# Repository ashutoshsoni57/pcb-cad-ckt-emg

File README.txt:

Autodesk EAGLE based EMG filtering circuit with
dual layer PCB Design.

Size:- 6x6 cm (length x breadth)
Reference 3D CAD images attached (Prepared from Fusion 360 pushed from EAGLE)

For printing check Toner Transfer Images.
Ground Polygon
Export BoM as required

Project under MIT LICENSE

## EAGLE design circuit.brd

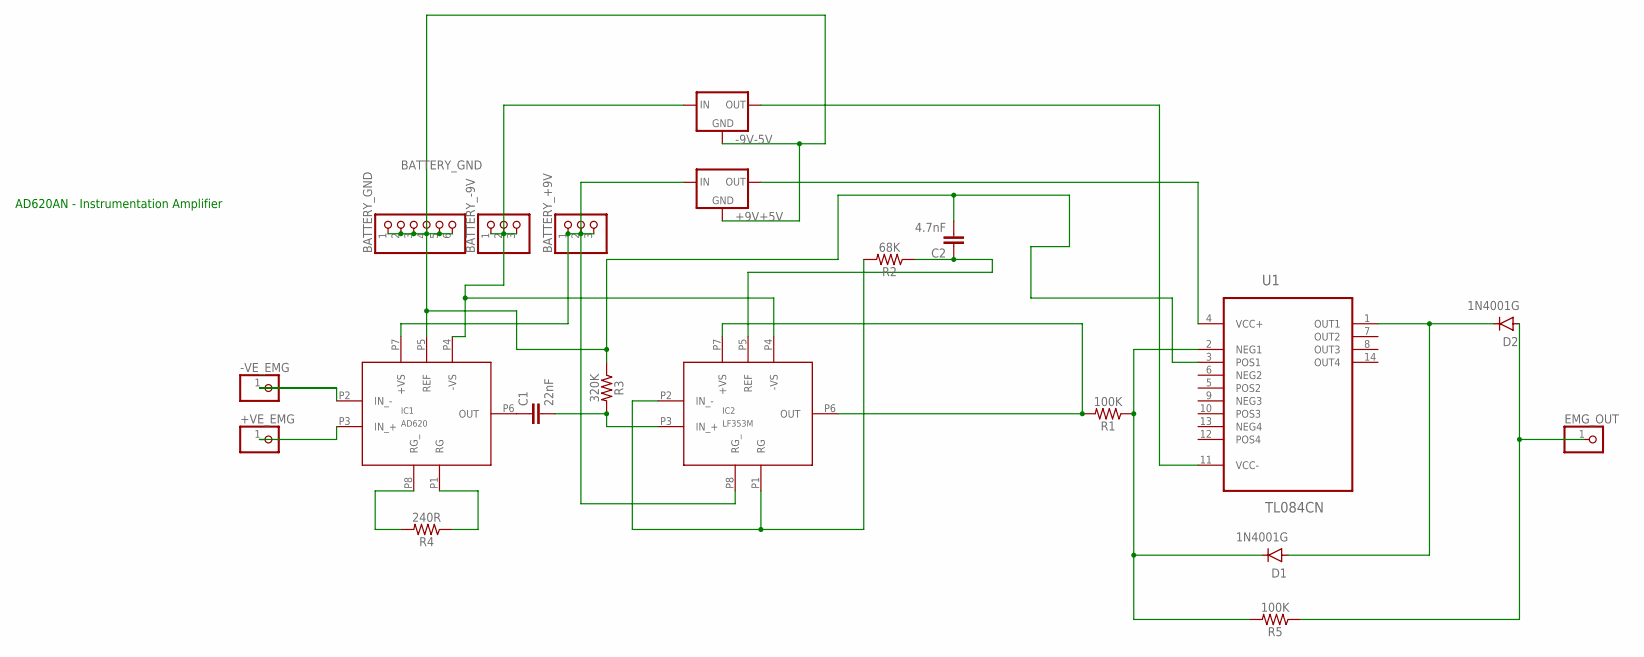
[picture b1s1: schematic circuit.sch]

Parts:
+9V+5V: 78XXL
+VE_EMG: PINHD-1X1; 1X01
-9V-5V: 78XXL
-VE_EMG: PINHD-1X1; 1X01
BATTERY_+9V: PINHD-1X3; 1X03
BATTERY_-9V: PINHD-1X3; 1X03
BATTERY_GND: PINHD-1X6; 1X06
C1: 22nF; CAP-PTH-10MM
C2: 4.7nF; CAP-PTH-10MM
D1, D2: 1N4001G; DO-41
EMG_OUT: PINHD-1X1; 1X01
IC1: AD620; DIL8
IC2: LF353M; DIL8
R1, R5: 100K; AXIAL-0.3
R2: 68K; AXIAL-0.3
R3: 320K; AXIAL-0.3
R4: 240R; AXIAL-0.3
U1: TL084CN; DIP254P762X510-14

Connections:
BATTERY_GND: +9V+5V.GND, -9V-5V.GND, BATTERY_GND.1, BATTERY_GND.2, BATTERY_GND.3, BATTERY_GND.4, BATTERY_GND.5, BATTERY_GND.6, C2.2, IC1.P5 (REF), R3.P$1 (1), U1.3 (POS1)
unnamed: IC1.P8 (RG_), R4.P$2 (2)
unnamed: IC1.P1 (RG), R4.P$1 (1)
unnamed: +VE_EMG.1, IC1.P3 (IN_+)
unnamed: -VE_EMG.1, IC1.P2 (IN_-)
unnamed: +9V+5V.IN, BATTERY_+9V.1, BATTERY_+9V.2, BATTERY_+9V.3, IC1.P7 (+VS), IC2.P8 (RG_)
unnamed: C1.1, IC1.P6 (OUT)
unnamed: D1.C, R1.P$1 (1), R5.P$2 (2), U1.2 (NEG1)
unnamed: C1.2, IC2.P3 (IN_+), R3.P$2 (2)
unnamed: IC2.P1 (RG), IC2.P2 (IN_-), R2.P$2 (2)
unnamed: C2.1, IC2.P5 (REF), R2.P$1 (1)
unnamed: IC2.P6 (OUT), IC2.P7 (+VS), R1.P$2 (2)
unnamed: D1.A, D2.C, U1.1 (OUT1)
unnamed: +9V+5V.OUT, U1.4 (VCC+)
unnamed: -9V-5V.OUT, U1.11 (VCC-)
unnamed: D2.A, EMG_OUT.1, R5.P$1 (1)
unnamed: -9V-5V.IN, BATTERY_-9V.1, BATTERY_-9V.2, BATTERY_-9V.3, IC1.P4 (-VS), IC2.P4 (-VS)

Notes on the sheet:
AD620AN - Instrumentation Amplifier

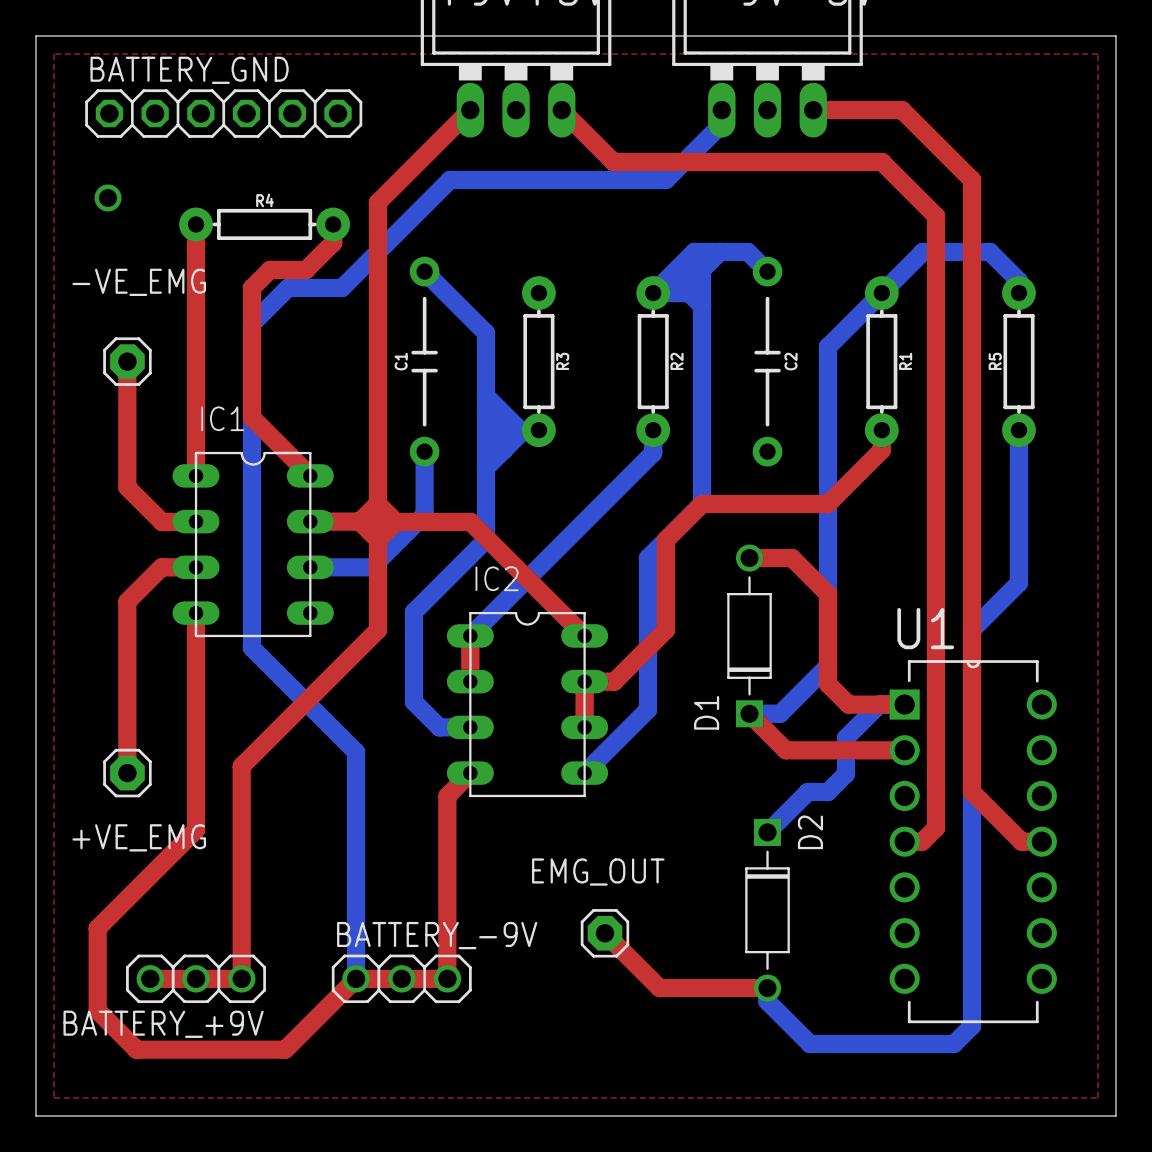
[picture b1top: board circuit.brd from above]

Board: 2 copper layers, 60.0 x 60.0 mm, 20 parts (0 on the bottom side), 17 nets.

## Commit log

2020-12-09 PCB Design for filtering Electromyogram Signals

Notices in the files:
parts and their libraries:
SparkFun-Capacitors: Licensing: Creative Commons ShareAlike 4.0 International - https://creativecommons.org/licenses/by-sa/4.0
